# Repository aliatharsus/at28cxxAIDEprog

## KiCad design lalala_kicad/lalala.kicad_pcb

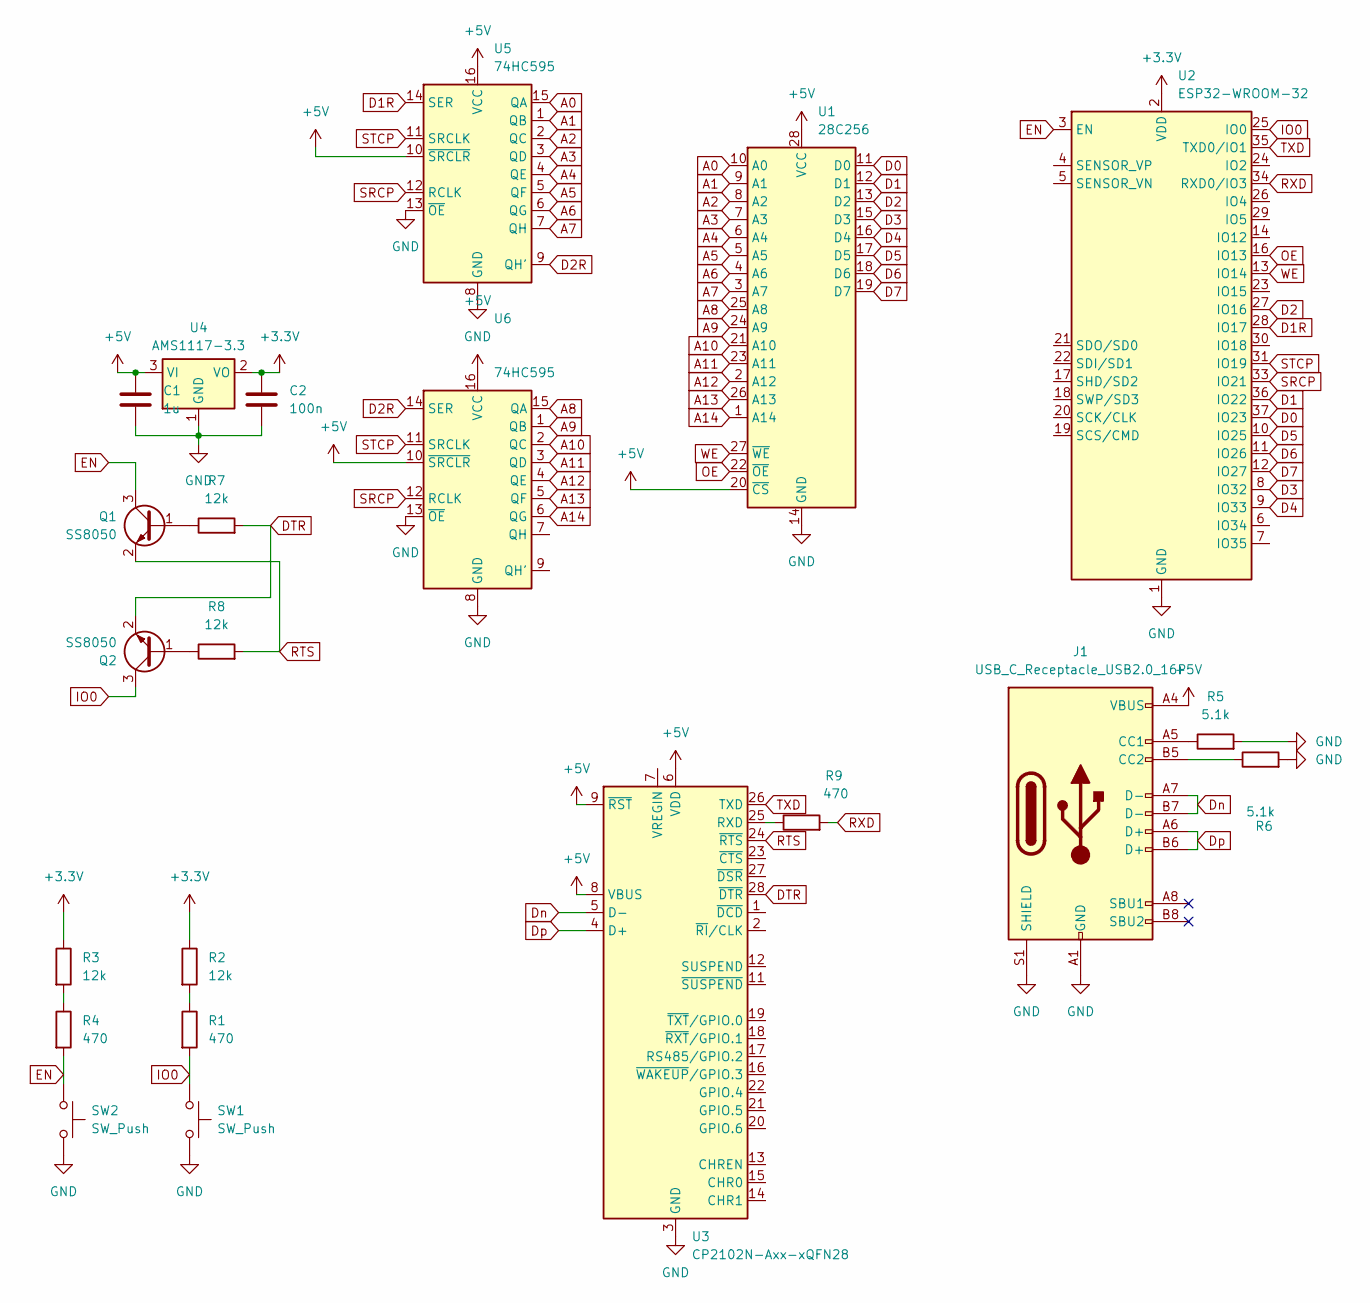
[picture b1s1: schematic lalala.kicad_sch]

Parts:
C1: 1u; C_0805_2012Metric
C2: 100n; C_0805_2012Metric
J1: USB_C_Receptacle_USB2.0_16P; USB_C_Receptacle_GCT_USB4105-xx-A_16P_TopMnt_Horizontal
Q1, Q2: SS8050; SOT-23
R1, R4, R9: 470; R_0805_2012Metric
R2, R3, R7, R8: 12k; R_0805_2012Metric
R5, R6: 5.1k; R_0805_2012Metric
SW1, SW2: SW_Push; SW_SPST_TL3342
U1: 28C256; DIP-28_W15.24mm_LongPads
U2: ESP32-WROOM-32
U3: CP2102N-Axx-xQFN28; QFN-28-1EP_5x5mm_P0.5mm_EP3.35x3.35mm
U4: AMS1117-3.3; SOT-223-3_TabPin2
U5, U6: 74HC595; DIP-16_W7.62mm_LongPads

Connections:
+3.3V: C2.1, R2.1, R3.1, U2.2 (VDD), U4.2 (VO)
+5V: C1.1, J1.A4 (VBUS), J1.A9 (VBUS), J1.B4 (VBUS), J1.B9 (VBUS), U1.20 (~CS), U1.28 (VCC), U3.6 (VDD), U3.8 (VBUS), U3.9 (~RST), U4.3 (VI), U5.10 (~SRCLR), U5.16 (VCC), U6.10 (~SRCLR), U6.16 (VCC)
A0: U1.10 (A0), U5.15 (QA)
A1: U1.9 (A1), U5.1 (QB)
A2: U1.8 (A2), U5.2 (QC)
A3: U1.7 (A3), U5.3 (QD)
A4: U1.6 (A4), U5.4 (QE)
A5: U1.5 (A5), U5.5 (QF)
A6: U1.4 (A6), U5.6 (QG)
A7: U1.3 (A7), U5.7 (QH)
A8: U1.25 (A8), U6.15 (QA)
A9: U1.24 (A9), U6.1 (QB)
A10: U1.21 (A10), U6.2 (QC)
A11: U1.23 (A11), U6.3 (QD)
A12: U1.2 (A12), U6.4 (QE)
A13: U1.26 (A13), U6.5 (QF)
A14: U1.1 (A14), U6.6 (QG)
D0: U1.11 (D0), U2.37 (IO23)
D1: U1.12 (D1), U2.36 (IO22)
D1R: U2.28 (IO17), U5.14 (SER)
D2: U1.13 (D2), U2.27 (IO16)
D2R: U5.9 (QH'), U6.14 (SER)
D3: U1.15 (D3), U2.8 (IO32)
D4: U1.16 (D4), U2.9 (IO33)
D5: U1.17 (D5), U2.10 (IO25)
D6: U1.18 (D6), U2.11 (IO26)
D7: U1.19 (D7), U2.12 (IO27)
DTR: Q2.2 (E), R7.2, U3.28 (~DTR)
Dn: J1.A7 (D-), J1.B7 (D-), U3.5 (D-)
Dp: J1.A6 (D+), J1.B6 (D+), U3.4 (D+)
EN: Q1.3 (C), R4.2, SW2.1, U2.3 (EN)
GND: C1.2, C2.2, J1.A1 (GND), J1.A12 (GND), J1.B1 (GND), J1.B12 (GND), J1.S1 (SHIELD), R5.2, R6.2, SW1.2, SW2.2, U1.14 (GND), U2.1 (GND), U2.15 (GND), U2.38 (GND), U2.39 (GND), U3.3 (GND), U3.29 (GND), U4.1 (GND), U5.8 (GND), U5.13 (~OE), U6.8 (GND), U6.13 (~OE)
IO0: Q2.3 (C), R1.2, SW1.1, U2.25 (IO0)
unnamed: J1.A5 (CC1), R5.1
unnamed: J1.B5 (CC2), R6.1
unnamed: Q1.1 (B), R7.1
unnamed: Q2.1 (B), R8.1
unnamed: R1.1, R2.2
unnamed: R3.2, R4.1
unnamed: R9.1, U3.25 (RXD)
OE: U1.22 (~OE), U2.16 (IO13)
RTS: Q1.2 (E), R8.2, U3.24 (~RTS)
RXD: R9.2, U2.34 (RXD0/IO3)
SRCP: U2.33 (IO21), U5.12 (RCLK), U6.12 (RCLK)
STCP: U2.31 (IO19), U5.11 (SRCLK), U6.11 (SRCLK)
TXD: U2.35 (TXD0/IO1), U3.26 (TXD)
WE: U1.27 (~WE), U2.13 (IO14)

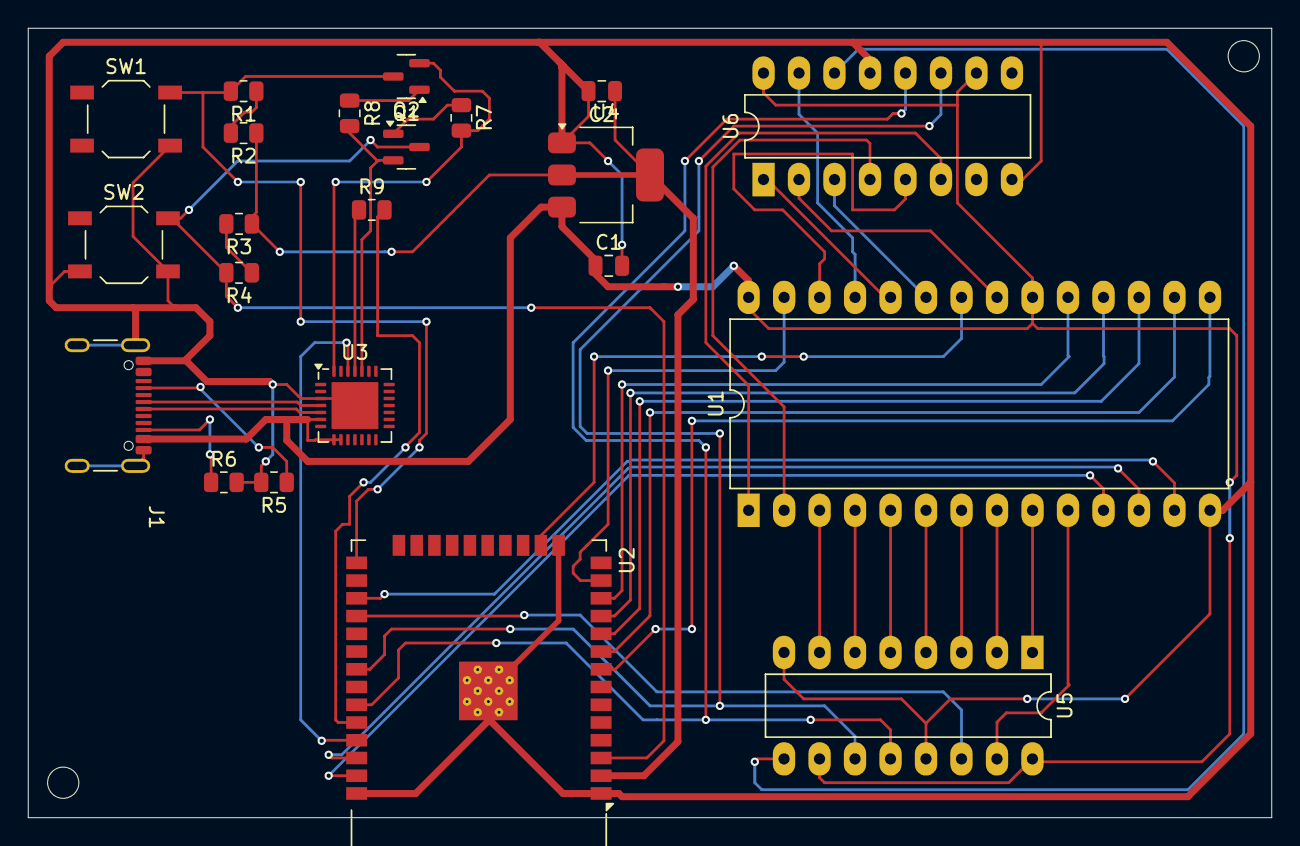
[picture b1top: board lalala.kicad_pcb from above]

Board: 2 copper layers, 89.0 x 56.5 mm, 22 parts (0 on the bottom side), 47 nets.

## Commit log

2025-07-05 Add project files
2025-07-07 Added .org support
2025-07-11 Added PCB (replace the ROM with a textool 28 pin test IC holder)
